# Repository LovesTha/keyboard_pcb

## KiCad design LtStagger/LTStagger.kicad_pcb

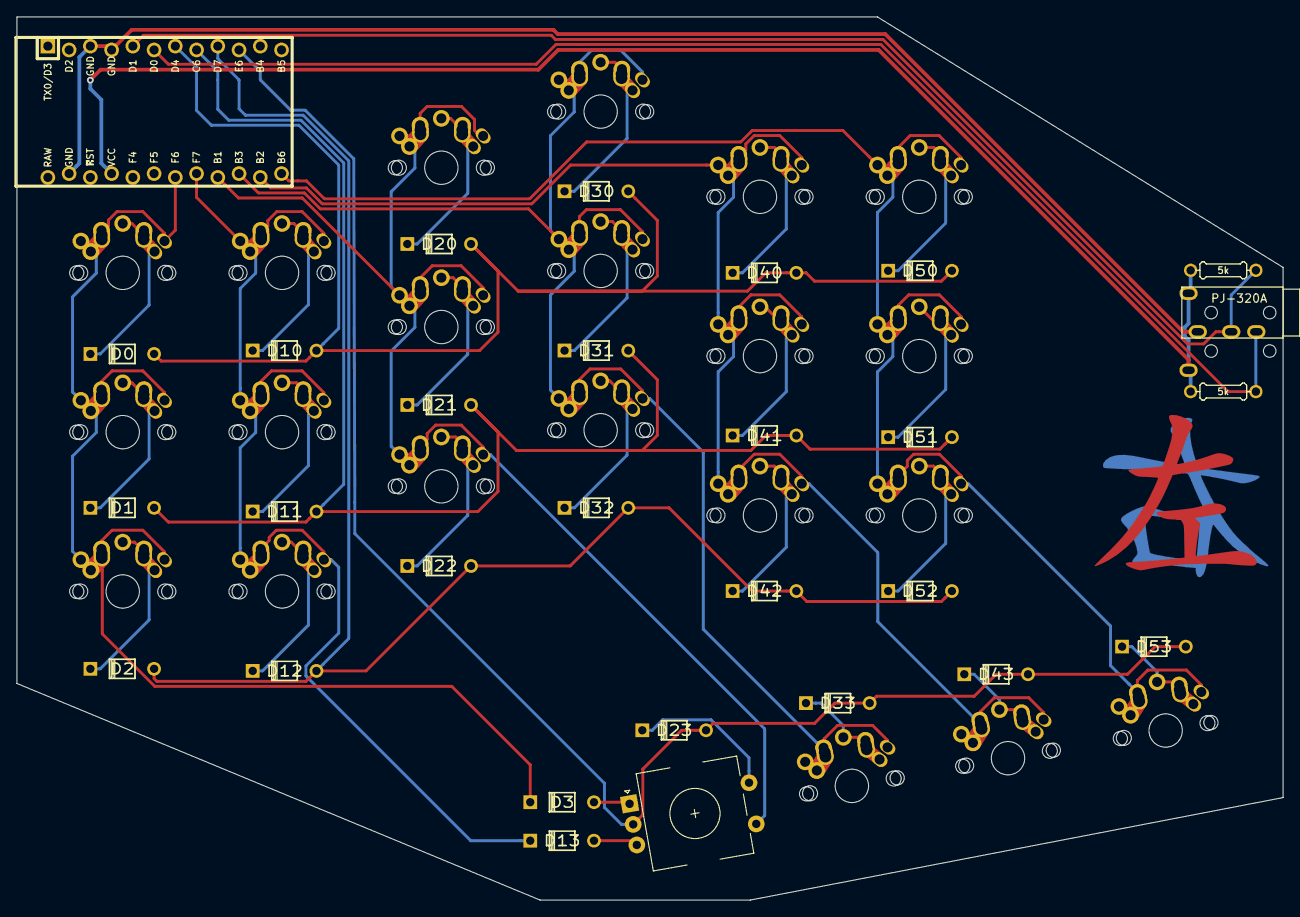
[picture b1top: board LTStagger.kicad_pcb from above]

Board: 2 copper layers, 151.4 x 105.6 mm, 50 parts (1 on the bottom side), 38 nets.

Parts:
D0, D1, D2: D; Diode
D3: D03; Diode
D10: D10; Diode
D11: D11; Diode
D12: D12; Diode
D13: D13; Diode
D20: D20; Diode
D21: D21; Diode
D22: D22; Diode
D23: D23; Diode
D30: D30; Diode
D31: D31; Diode
D32: D32; Diode
D33: D33; Diode
D40: D40; Diode
D41: D41; Diode
D42: D42; Diode
D43: D43; Diode
D50: D50; Diode
D51: D51; Diode
D52: D52; Diode
D53: D53; Diode
K0: K00; Triple-Dual-1u
K1: K01; Triple-Dual-1u
K2: K02; Triple-Dual-1u
K10: K10; Triple-Dual-1u
K11: K11; Triple-Dual-1u
K12: K12; Triple-Dual-1u
K20: K20; Triple-Dual-1u
K21: K21; Triple-Dual-1u
K22: K22; Triple-Dual-1u
K30: K30; Triple-Dual-1u
K31: K31; Triple-Dual-1u
K32: K32; Triple-Dual-1u
K33: K33; Triple-Dual-1u
K40: K40; Triple-Dual-1u
K41: K41; Triple-Dual-1u
K42: K42; Triple-Dual-1u
K43: K43; Triple-Dual-1u
K50: K50; Triple-Dual-1u
K51: K51; Triple-Dual-1u
K53: K53; Triple-Dual-1u
L52: K52; Triple-Dual-1u
R4, R5: 5k; Resistor-Compact
SW1: Rotary_Encoder_Switch; RotaryEncoder_EC11
U1: ProMicro; ArduinoProMicro-ZigZag
U2: TRRS; TRRS-PJ-320A-dual

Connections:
Col0: D3.2, K0.1, K1.1, K2.1, U1.18
Col1: D13.2, K10.1, K11.1, K12.1, U1.17
Col2: K20.1, K21.1, K22.1, SW1.S1, U1.16
Col3: K30.1, K31.1, K32.1, K33.1, U1.15
Col4: K40.1, K41.1, K42.1, K43.1, U1.14
Col5: K50.1, K51.1, K53.1, L52.1, U1.13
GND: U1.3, U1.4, U1.23, U2.2
unnamed: D0.2, K0.2
unnamed: D1.2, K1.2
unnamed: D2.2, K2.2
unnamed: D3.1, SW1.A
unnamed: D10.2, K10.2
unnamed: D11.2, K11.2
unnamed: D12.2, K12.2
unnamed: D13.1, SW1.B
unnamed: D20.2, K20.2
unnamed: D21.2, K21.2
unnamed: D22.2, K22.2
unnamed: D23.2, SW1.S2
unnamed: D30.2, K30.2
unnamed: D31.2, K31.2
unnamed: D32.2, K32.2
unnamed: D33.2, K33.2
unnamed: D40.2, K40.2
unnamed: D41.2, K41.2
unnamed: D42.2, K42.2
unnamed: D43.2, K43.2
unnamed: D50.2, K50.2
unnamed: D51.2, K51.2
unnamed: D52.2, L52.2
unnamed: D53.2, K53.2
Row0: D0.1, D10.1, D20.1, D30.1, D40.1, D50.1, U1.7
Row1: D1.1, D11.1, D21.1, D31.1, D41.1, D51.1, U1.8
Row2: D2.1, D12.1, D22.1, D32.1, D42.1, D52.1, U1.9
Row3: D23.1, D33.1, D43.1, D53.1, SW1.C, U1.10
SCL: R5.2, U1.5, U2.3
SDA: R4.2, U1.6, U2.4
VCC: R4.1, R5.1, U1.21, U2.1

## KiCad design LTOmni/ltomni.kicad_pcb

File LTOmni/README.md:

# LTOmni (prototype)

[Layout Intent](http://www.keyboard-layout-editor.com/##@@_a:7;&=&=Num%20Lock&_a:4;&=7%0AHome&=8%0A%E2%86%91&=9%0APgUp&_h:2;&=+&_x:0.75&a:7;&=;&@=&=//&_a:4;&=4%0A%E2%86%90&=5&=6%0A%E2%86%92&_x:1.75&a:7;&=;&@=&=*&_a:4;&=1%0AEnd&=2%0A%E2%86%93&=3%0APgDn&_c=#a1ad13&h:2;&=Enter%0A%0A%0A%0A%0A%0A%0A%0A%0Ak35b1&_x:0.75&c=#cccccc&a:7;&=;&@_c=#9e0b0b&w:2;&=K30b2&_c=#cf7ecb&a:4&w:2;&=0%0AIns%0A%0A%0A%0A%0A%0A%0A%0Ak32b1&_c=#1a3ebd;&=.%0ADel%0A%0A%0A%0A%0A%0A%0A%0Ak34&_x:1.75&c=#a1ad13&a:7;&=k35;&@_y:0.25&c=#9e0b0b&w:1.25;&=k30b1&_c=#5134c7&w:1.25;&=k31b2&_c=#cf7ecb&w:1.25;&=k33b1&_c=#1a3ebd&w:1.25;&=k31b1;&@_c=#9e0b0b;&=k30&_c=#5134c7;&=k31&_c=#22bdb3;&=k32&_c=#cf7ecb;&=k33;&@_x:1&c=#5134c7&w:1.25;&=k31b1&_c=#cf7ecb&w:1.25;&=k32b2&_c=#1a3ebd&w:1.25;&=k34c1&_c=#a1ad13&w:1.25;&=k35c2)  
[Layout Images](https://imgur.com/a/m8PkLg1)

## Discord

https://discord.gg/E5jSgM

## License

[CC-BY-NC](https://creativecommons.org/licenses/by-nc/4.0/)

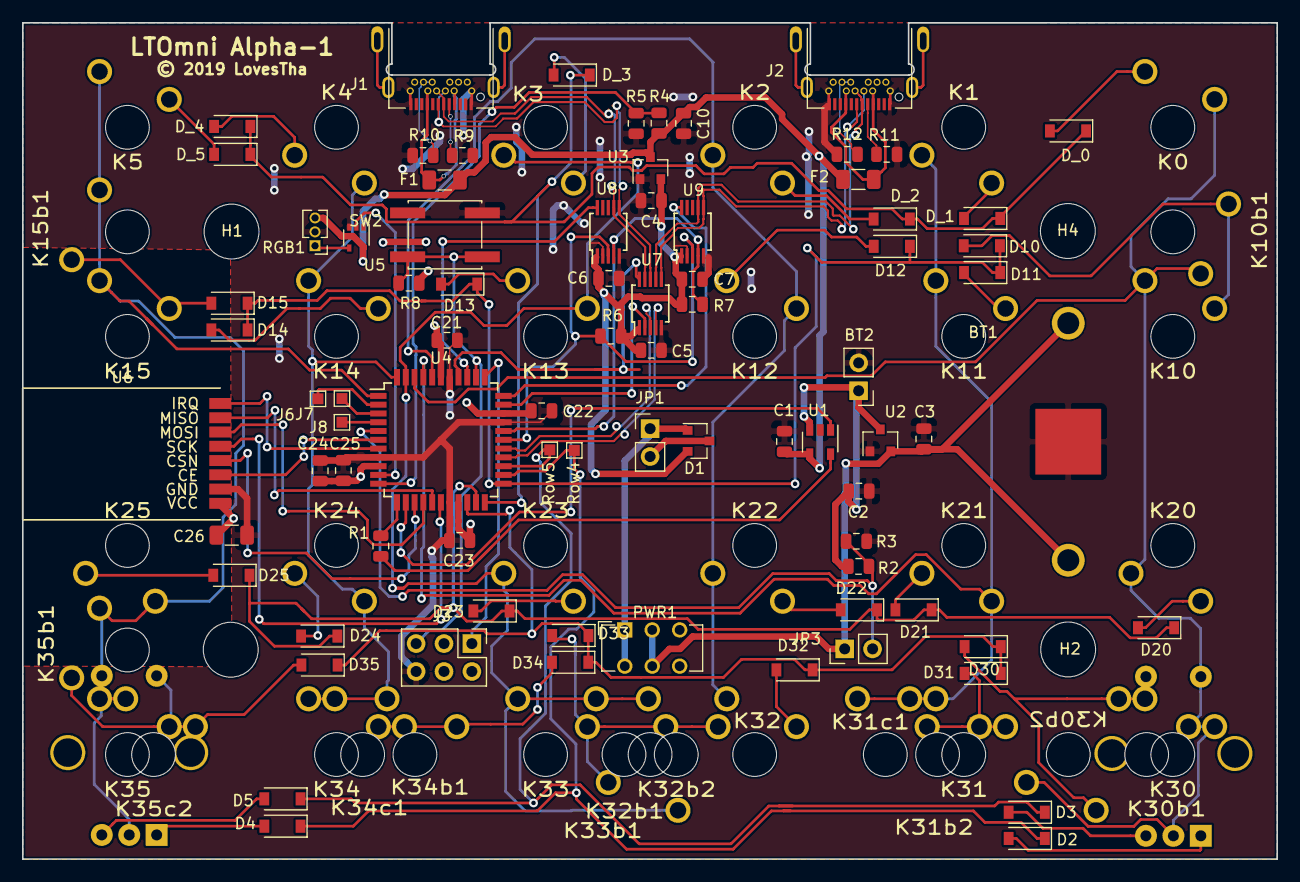
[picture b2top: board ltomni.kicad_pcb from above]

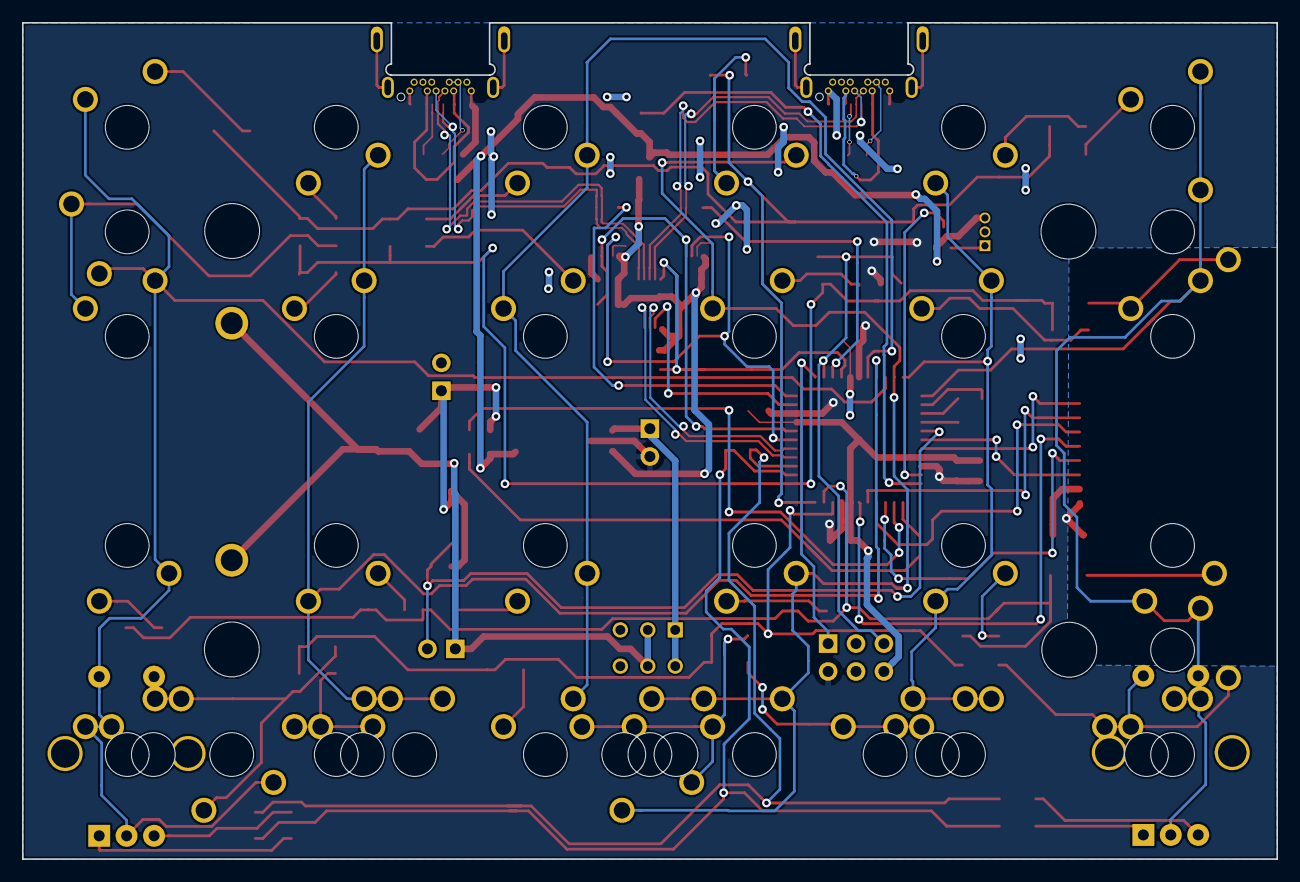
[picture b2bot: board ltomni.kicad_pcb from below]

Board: 2 copper layers, 114.3 x 76.2 mm, 124 parts (39 on the bottom side), 82 nets.

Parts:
BT1: Battery; BK-913
BT2: Battery_Cell; PinHeader_1x02_P2.54mm_Vertical
C1, C2: 4.7uF; C_0805_2012Metric
C3, C4: 1uF; C_0805_2012Metric
C5, C6, C7, C10, C21, C22, C23, C24: 0.1uF; C_0805_2012Metric
C25: 10uF; C_0805_2012Metric
C26: 47uF; C_1206_3216Metric
D1: D_Schottky_x2_KCom_AAK; SOT-23
D2, D3, D4, D5, D10, D11, D12, D13, D14, D15, D20, D21, D22, D23, D24, D25, D30, D31, D32, D33, D34, D35: D; D_SOD-123
D_0, D_1, D_2, D_3, D_4, D_5: D; D_SOD-123
F1, F2: Fuse; R_1206_3216Metric
H1, H2, H3, H4: MountingHole; MountingHole_5mm
J1, J2: USB_C_Receptacle; USB_C_Receptacle_JAE_DX07B024XJ1_cuts
J3: TC2030-IDC; PinHeader_2x03_P2.54mm_Vertical
J6: A6; TestPoint_Pad_1.0x1.0mm
J7: A7; TestPoint_Pad_1.0x1.0mm
J8: B0; TestPoint_Pad_1.0x1.0mm
JP1: NO USB; PinHeader_1x02_P2.54mm_Vertical
JP3: BATT CHECK; PinHeader_1x02_P2.54mm_Vertical
K0: K00; MX_Plate_100H
K1: K01; MX_Plate_100H
K2: K02; MX_Plate_100H
K3: K03; MX_Plate_100H
K4: K04; MX_Plate_100H
K5: K05; MX_Plate_100H
K10: K10; MX_Plate_100H
K10b1: K10b; MX_Plate_200V
K11: K11; MX_Plate_100H
K12: K12; MX_Plate_100H
K13: K13; MX_Plate_100H
K14: K14; MX_Plate_100H
K15: K15; MX_Plate_100H
K15b1: K15b; MX_Plate_200V
K20: K20; MX_Plate_100H
K21: K21; MX_Plate_100H
K22: K22; MX_Plate_100H
K23: K23; MX_Plate_100H
K24: K24; MX_Plate_100H
K25: K25; MX_Plate_100H
K30: K30; MX_Plate_100H
K30b1: K30b; MX_Plate_125H
K30b2: K30b2; MX_Plate_200H
K31: K31; MX_Plate_100H
K31b2: K31b; MX_Plate_125H
K31c1: K31c; MX_Plate_125H
K32: K32; MX_Plate_100H
K32b1: K32b1; MX_Plate_200H
K32b2: K32b2; MX_Plate_125H
K33: K33; MX_Plate_100H
K33b1: K33b; MX_Plate_125H
K34: K34; MX_Plate_100H
K34b1: K34b; MX_Plate_125H
K34c1: K34c; MX_Plate_125H
K35: K35; MX_Plate_100H
K35b1: K35b; MX_Plate_200V
K35c2: K35c; MX_Plate_125H
PWR1: Switch-6P-2S2T; SW_CuK_JS202011CQN_DPDT_Straight
R1, R6, R7, R8: 10k; R_0805_2012Metric
R2, R3: 470k; R_0805_2012Metric
R4, R5: 100k; R_0805_2012Metric
R9, R10, R11, R12: 5.1k; R_0805_2012Metric
RGB1: Conn_01x03_Male; PinHeader_1x03_P1.27mm_Vertical
Row4: D4; TestPoint_Pad_1.0x1.0mm
Row5: D5; TestPoint_Pad_1.0x1.0mm
SW1, SW3: Rotary_Encoder_Switch; RotaryEncoder_Alps_EC11E-Switch_Vertical_H20mm_CircularMoun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
SW2: SW_Push; SW_SPST_EVQQ2
U1: MCP73831; SOT-23-5
U2: MCP1700 (3.0V); SOT-23
U3: MCP1700 (3.3V); SOT-23
U4: ATXMEGA-A4U-EPAD; TQFP-44_10x10mm_P0.8mm
U5: 74LVC1G34; SOT-353_SC-70-5
U6: nRF24L01_module; nRF24L01
U7, U8, U9: FSUSB42; MSOP-10_3x3mm_P0.5mm

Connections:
+3V3: C4.2, C5.1, C6.1, C7.1, D1.2, R6.2, R7.1, U3.2, U7.1, U8.1, U9.1
+5V: C1.1, C10.1, F1.2, F2.2, R4.1, RGB1.3, U1.4, U3.3, U5.5
+BATT: D1.1, JP1.1, PWR1.1, PWR1.4
/A6: J6.1, U4.2
/A7: J7.1, U4.3
/B0: J8.1, U4.4
/BATT_IN: BT1.1, C3.2, JP3.1, PWR1.2, PWR1.5, U2.2
/BAT_LI_ION: BT2.1, C2.1, R2.1, U1.3, U2.3
/BAT_LVL: JP3.2, R2.2, R3.1, U4.5
/BAT_PROG: R1.2, U4.12
/BAT_STAT: U1.1, U4.13
/CE: U4.6, U6.3
/COL0: K0.2, K10.1, K10b1.2, K20.2, K30.2, K30b1.2, K30b2.2, SW1.C, SW1.S2, U4.42
/COL1: K1.2, K11.1, K21.1, K31.1, K31b2.1, K31c1.1, U4.41
/COL2: K2.2, K12.2, K22.2, K32.1, U4.40
/COL3: K3.2, K13.2, K23.2, K32b1.1, K32b2.1, K33.1, K33b1.1, U4.43
/COL4: K4.1, K14.1, K24.1, K34.1, K34b1.1, K34c1.1, U4.44
/COL5: K5.1, K15.1, K15b1.2, K25.1, K35.1, K35b1.2, K35c2.1, SW3.C, SW3.S1, U4.1
/CSN: U4.14, U6.4
/D4: D2.1, D4.1, Row4.1, U4.24
/D5: D3.1, D5.1, Row5.1, U4.25
/D+: U4.27, U7.3
/D-: U4.26, U7.4
/I2C_LEFT: U4.36, U8.10
/I2C_RIGHT: U4.33, U9.10
/IRQ: U4.7, U6.8
/MISO: U4.16, U6.7
/MOSI: U4.15, U6.6
/PDI: J3.1, U4.34
/ROW0: D_0.1, D_1.1, D_2.1, D_3.1, D_4.1, D_5.1, U4.22
/ROW1: D10.1, D11.1, D12.1, D13.1, D14.1, D15.1, U4.23
/ROW2: D20.1, D21.1, D22.1, D23.1, D24.1, D25.1, U4.21
/ROW3: D30.1, D31.1, D32.1, D33.1, D34.1, D35.1, U4.20
/RST: J3.5, R8.2, SW2.2, U4.35
/SCK: U4.17, U6.5
/SCL: R7.2, U4.29, U8.4, U9.4
/SDA: R6.1, U4.28, U8.3, U9.3
/UNDER_LED: U4.10, U5.2
/USB_L_D+: J1.A6, J1.B6, U7.9, U8.7
/USB_L_D-: J1.A7, J1.B7, U7.8, U8.6
/USB_OE: U4.37, U7.10
/USB_R_D+: J2.A6, J2.B6, U7.7, U9.7
/USB_R_D-: J2.A7, J2.B7, U7.6, U9.6
/USB_SEL: U4.32, U7.2
/VBUS_CHECK: R4.2, R5.1, U4.11
GND: BT1.2, BT2.2, C1.2, C2.2, C3.1, C4.1, C5.2, C6.2, C7.2, C10.2, C21.1, C22.1, C23.1, C24.1, C25.1, C26.1, J1.A1, J1.A12, J1.B1, J1.B12, J2.A1, J2.A12, J2.B1, J2.B12, J3.6, R3.2, R5.2, R9.2, R10.2, R11.2, R12.2, RGB1.2, SW2.1, U1.2, U2.1, U3.1, U4.8, U4.18, U4.30, U4.38, U5.3, U6.2, U7.5, U8.2, U8.5, U9.2, U9.5
unnamed: D2.2, SW1.A
unnamed: D3.2, SW1.B
unnamed: D4.2, SW3.A
unnamed: D5.2, SW3.B
unnamed: D10.2, K10.2, K10b1.1
unnamed: D11.2, K11.2
unnamed: D12.2, K12.1
unnamed: D13.2, K13.1
unnamed: D14.2, K14.2
unnamed: D15.2, K15.2, K15b1.1
unnamed: D20.2, K20.1
unnamed: D21.2, K21.2
unnamed: D22.2, K22.1
unnamed: D23.2, K23.1
unnamed: D24.2, K24.2
unnamed: D25.2, K25.2
unnamed: D30.2, K30.1, K30b1.1, K30b2.1, SW1.S1
unnamed: D31.2, K31.2, K31b2.2, K31c1.2
unnamed: D32.2, K32.2
unnamed: D33.2, K32b1.2, K32b2.2, K33.2, K33b1.2
unnamed: D34.2, K34.2, K34b1.2, K34c1.2
unnamed: D35.2, K35.2, K35b1.1, K35c2.2, SW3.S2
unnamed: D_0.2, K0.1
unnamed: D_1.2, K1.1
unnamed: D_2.2, K2.1
unnamed: D_3.2, K3.1
unnamed: D_4.2, K4.2
unnamed: D_5.2, K5.2
unnamed: J1.A5, R9.1
unnamed: J1.B3, J1.B5, R10.1
unnamed: J2.A5, R11.1
unnamed: J2.B3, J2.B5, R12.1
unnamed: RGB1.1, U5.4
unnamed: R1.1, U1.5
VBUS: F1.1, F2.1, J1.A4, J1.A9, J1.B4, J1.B9, J2.A4, J2.A9, J2.B4, J2.B9
VCC: C21.2, C22.2, C23.2, C24.2, C25.2, C26.2, D1.3, J3.2, JP1.2, R8.1, U4.9, U4.19, U4.31, U4.39, U6.1

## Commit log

2018-10-15 Basic schematic conversion yo Kicad v5
2018-11-06 Early work towards the LTFloater
2018-11-09 Complete PCB, DRC violations limited to USB-C
2018-11-11 Completely reworked PCB, with switches on the correct side, traces running mostly parrallel on a single side of the PCB
2018-11-11 Now with 8 underglow LEDs on the PCB
2018-11-11 All switches on the one side
2018-11-11 Trying to be better for visitors
2018-11-11 working image link
2018-11-11 working image link?
2018-11-11 Deleting temporary file
2019-01-01 A 6x4 that supports 5 key bottom rows and both landscape and portrait numpads
2019-01-01 Deleted old projects that I'm not interested in
2019-01-18 Before adding rotary encoders
2019-01-18 now with rotary encoder
2019-01-18 Discord
2019-01-21 maybe a final design?
2019-02-08 Rotated the diodes to all be the same way around
    Also added switch labels on the back, might be too many labels.
    Title and copyright moved to top left corner.
2020-01-18 the initial production files
2020-01-18 Initial PCB Missing pull up resistors for SPI
2020-08-04 Initial LTStagger
2020-08-06 About to even out the side bezels
2020-08-07 Ready for first review
2020-08-09 about to give an angle and dog bones
2020-08-11 dog bones and curve
2020-08-12 Maybe ready for production
2020-08-12 Plate footprint on the right layer
2020-08-13 new footprints
2024-02-28 Unknown status, but this is how I found it today.
2024-03-30 LTStagger 2, but that joystick is a bad idea
2024-04-19 Time to test footprints
2024-04-23 Libraries

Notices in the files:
LTOmni/ltomni.kicad_pcb:
© 2019 LovesTha
